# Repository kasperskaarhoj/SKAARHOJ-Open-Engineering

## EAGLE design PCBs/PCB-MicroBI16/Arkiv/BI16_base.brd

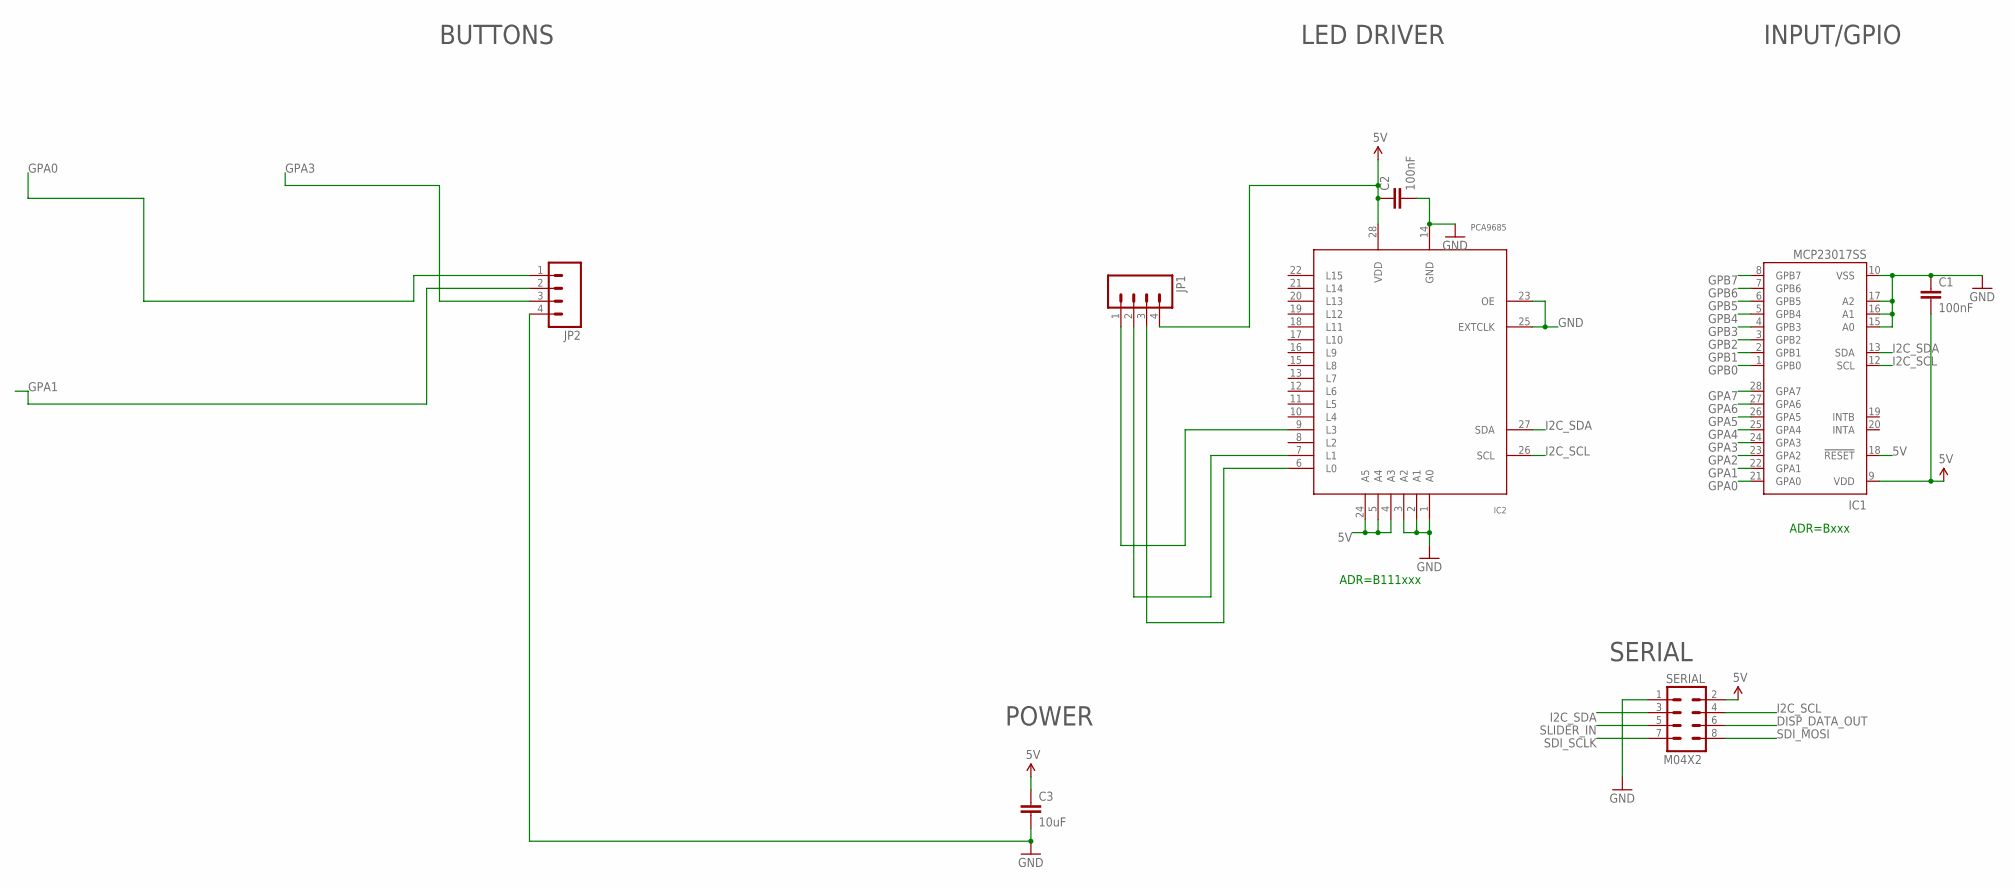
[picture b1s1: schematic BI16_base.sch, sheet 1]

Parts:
C1, C2: 100nF; 0603-CAP
C3: 10uF; 0805
IC1: MCP23017SS; SSOP28; MPN MCP23017-E/SS
IC2: PCA9685; TSSOP28
JP1, JP2: M04LOCK; 1X04_LOCK
SERIAL: M04X2; 2X4

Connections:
5V: C1.2, C2.1, C3.1, IC1.9 (VDD), IC1.18 (!RESET), IC2.4 (A3), IC2.5 (A4), IC2.24 (A5), IC2.28 (VDD), JP1.4, SERIAL.2
DISP_DATA_OUT: SERIAL.6
GND: C1.1, C2.2, C3.2, IC1.10 (VSS), IC1.15 (A0), IC1.16 (A1), IC1.17 (A2), IC2.1 (A0), IC2.2 (A1), IC2.3 (A2), IC2.14 (GND), IC2.23 (OE), IC2.25 (EXTCLK), JP2.4, SERIAL.1
GPA0: IC1.21 (GPA0), JP2.1
GPA1: IC1.22 (GPA1), JP2.2
GPA2: IC1.23 (GPA2)
GPA3: IC1.24 (GPA3), JP2.3
GPA4: IC1.25 (GPA4)
GPA5: IC1.26 (GPA5)
GPA6: IC1.27 (GPA6)
GPA7: IC1.28 (GPA7)
GPB0: IC1.1 (GPB0)
GPB1: IC1.2 (GPB1)
GPB2: IC1.3 (GPB2)
GPB3: IC1.4 (GPB3)
GPB4: IC1.5 (GPB4)
GPB5: IC1.6 (GPB5)
GPB6: IC1.7 (GPB6)
GPB7: IC1.8 (GPB7)
I2C_SCL: IC1.12 (SCL), IC2.26 (SCL), SERIAL.4
I2C_SDA: IC1.13 (SDA), IC2.27 (SDA), SERIAL.3
unnamed: IC2.9 (L3), JP1.1
unnamed: IC2.7 (L1), JP1.2
unnamed: IC2.6 (L0), JP1.3
SDI_MOSI: SERIAL.8
SDI_SCLK: SERIAL.7
SLIDER_IN: SERIAL.5

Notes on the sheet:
ADR=B111xxx
ADR=Bxxx
BUTTONS
LED DRIVER
INPUT/GPIO
POWER
SERIAL

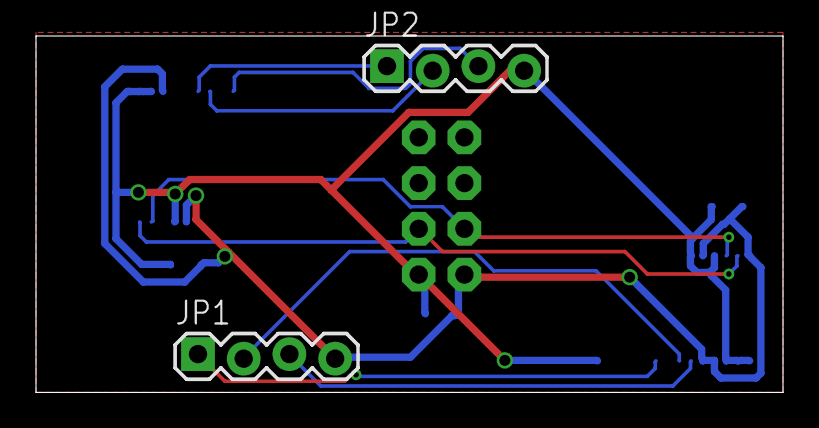
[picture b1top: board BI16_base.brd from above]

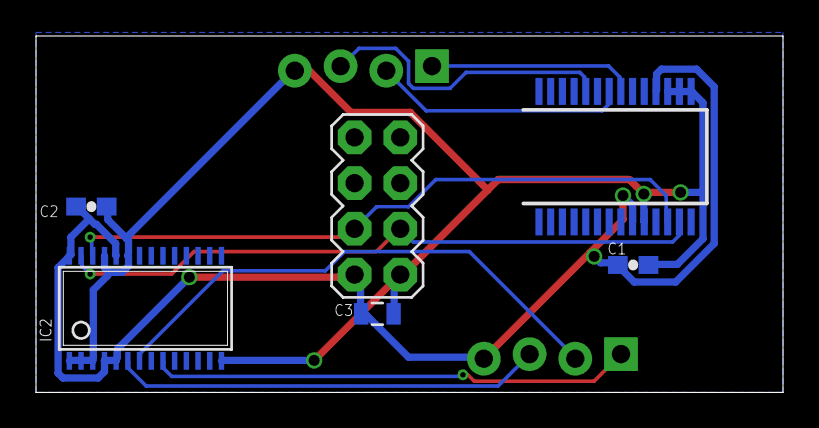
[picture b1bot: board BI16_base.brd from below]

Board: 2 copper layers, 41.5 x 19.8 mm, 8 parts (6 on the bottom side), 10 nets.

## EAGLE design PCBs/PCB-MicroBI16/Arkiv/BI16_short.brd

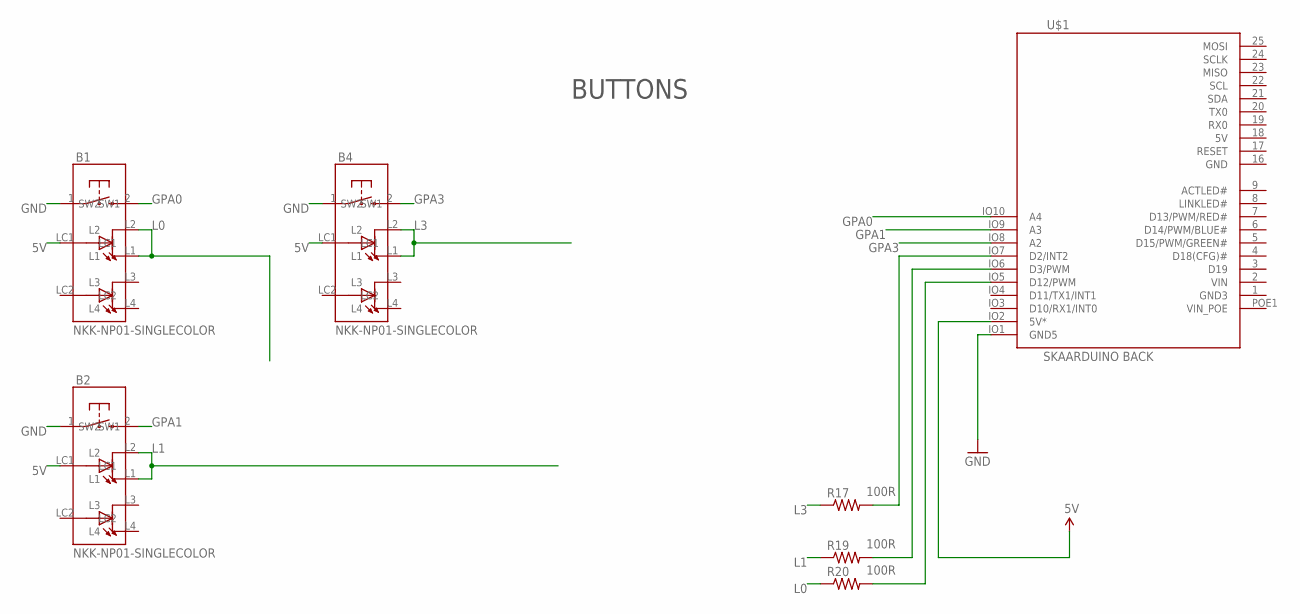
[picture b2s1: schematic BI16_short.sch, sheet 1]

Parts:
B1, B2, B4: NKK-NP01-SINGLECOLOR; NKK-NP01
R17, R19, R20: 100R; 0603-RES
U$1: SKAARDUINO_BACK_EDGECON; SKAARDUINO_BACK_PTH_EDGECON

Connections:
5V: B1.LC1, B2.LC1, B4.LC1, U$1.18 (5V), U$1.IO2 (5V*)
GND: B1.1 (SW1), B2.1 (SW1), B4.1 (SW1), U$1.16 (GND), U$1.IO1 (GND5)
GND3: U$1.1 (GND3)
GPA0: B1.2 (SW2), U$1.IO10 (A4)
GPA1: B2.2 (SW2), U$1.IO9 (A3)
GPA3: B4.2 (SW2), U$1.IO8 (A2)
L0: B1.L1, B1.L2, R20.1
L1: B2.L1, B2.L2, R19.1
L3: B4.L1, B4.L2, R17.1
unnamed: R17.2, U$1.IO7 (D2/INT2)
unnamed: R19.2, U$1.IO6 (D3/PWM)
unnamed: R20.2, U$1.IO5 (D12/PWM)
VIN: U$1.2 (VIN)
VIN_POE: U$1.POE1 (VIN_POE)

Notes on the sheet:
BUTTONS

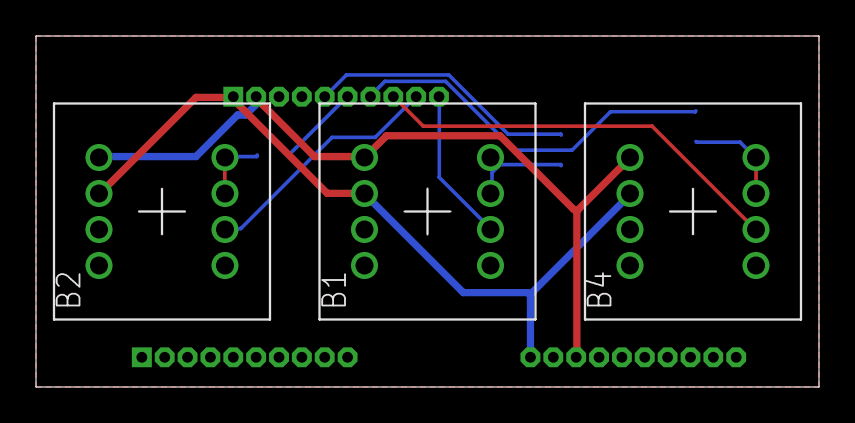
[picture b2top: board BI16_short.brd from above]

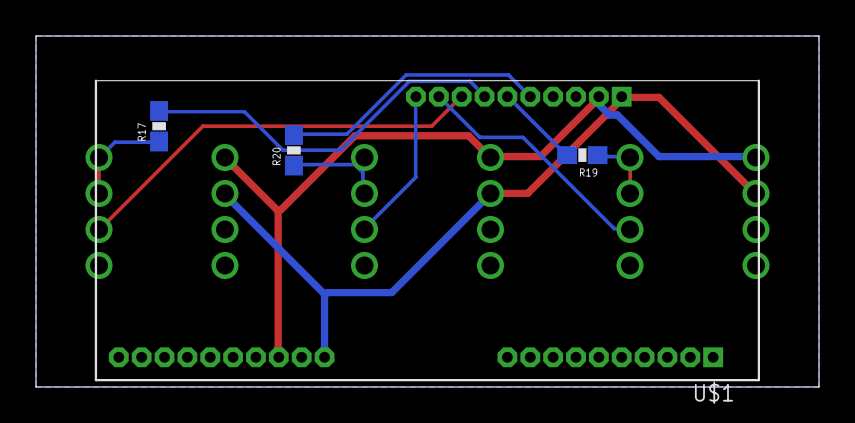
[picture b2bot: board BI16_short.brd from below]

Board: 2 copper layers, 43.5 x 19.5 mm, 7 parts (4 on the bottom side), 11 nets.

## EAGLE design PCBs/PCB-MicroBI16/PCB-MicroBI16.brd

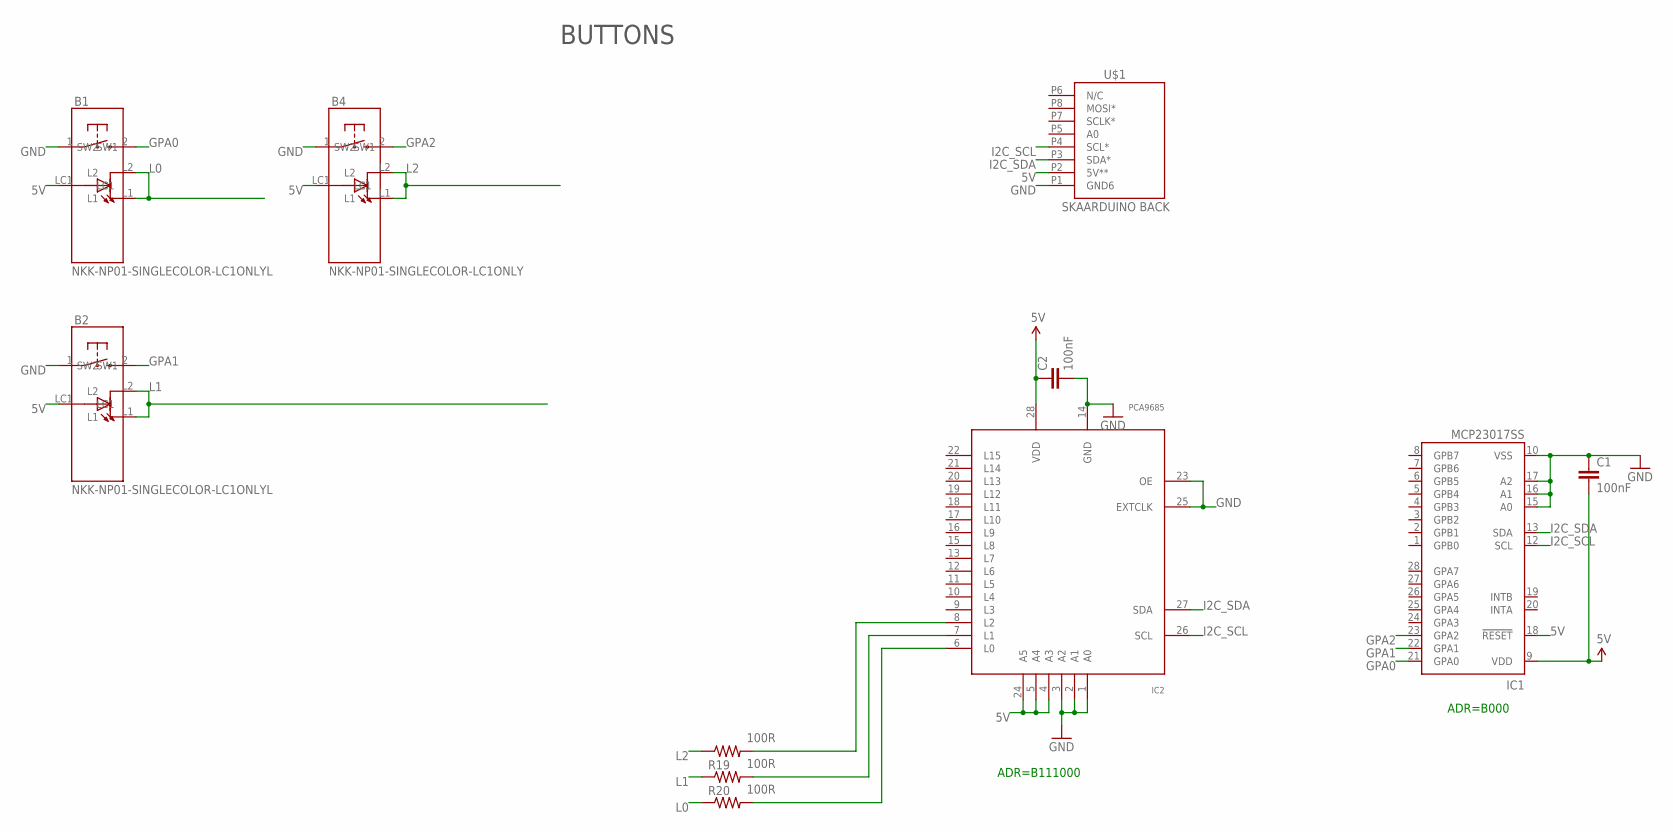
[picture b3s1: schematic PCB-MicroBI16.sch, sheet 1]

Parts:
B1, B2: NKK-NP01-SINGLECOLOR-LC1ONLYL; NKK-NP01_LESSHOLES3
B4: NKK-NP01-SINGLECOLOR-LC1ONLY; NKK-NP01_LESSHOLES2
C1, C2: 100nF; 0603-CAP
IC1: MCP23017SS; SSOP28; MPN MCP23017-E/SS
IC2: PCA9685; TSSOP28
R18, R19, R20: 100R; 0603-RES
U$1: SKAARDUINO_BACK_SERIAL; SKAARDUINO_BACK_PTH_SERIAL

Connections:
5V: B1.LC1, B2.LC1, B4.LC1, C1.2, C2.1, IC1.9 (VDD), IC1.18 (!RESET), IC2.4 (A3), IC2.5 (A4), IC2.24 (A5), IC2.28 (VDD), U$1.P2 (5V**)
GND: B1.1 (SW1), B2.1 (SW1), B4.1 (SW1), C1.1, C2.2, IC1.10 (VSS), IC1.15 (A0), IC1.16 (A1), IC1.17 (A2), IC2.1 (A0), IC2.2 (A1), IC2.3 (A2), IC2.14 (GND), IC2.23 (OE), IC2.25 (EXTCLK), U$1.P1 (GND6)
GPA0: B1.2 (SW2), IC1.21 (GPA0)
GPA1: B2.2 (SW2), IC1.22 (GPA1)
GPA2: B4.2 (SW2), IC1.23 (GPA2)
I2C_SCL: IC1.12 (SCL), IC2.26 (SCL), U$1.P4 (SCL*)
I2C_SDA: IC1.13 (SDA), IC2.27 (SDA), U$1.P3 (SDA*)
L0: B1.L1, B1.L2, R20.1
L1: B2.L1, B2.L2, R19.1
L2: B4.L1, B4.L2, R18.1
unnamed: IC2.8 (L2), R18.2
unnamed: IC2.7 (L1), R19.2
unnamed: IC2.6 (L0), R20.2

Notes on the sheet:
BUTTONS
ADR=B111000
ADR=B000

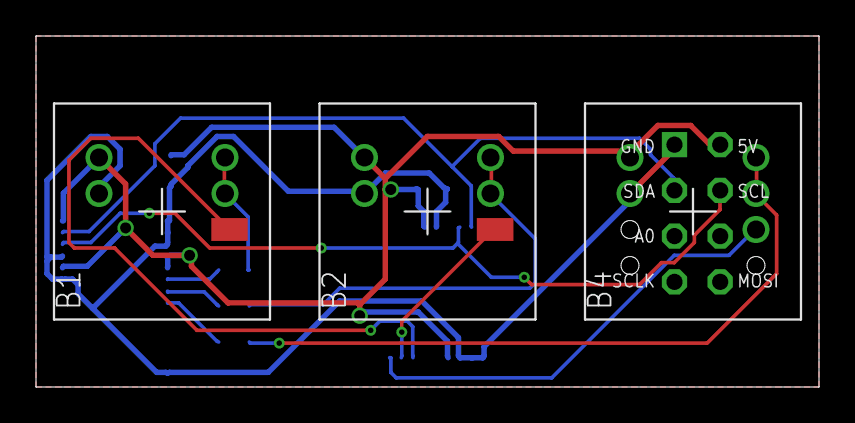
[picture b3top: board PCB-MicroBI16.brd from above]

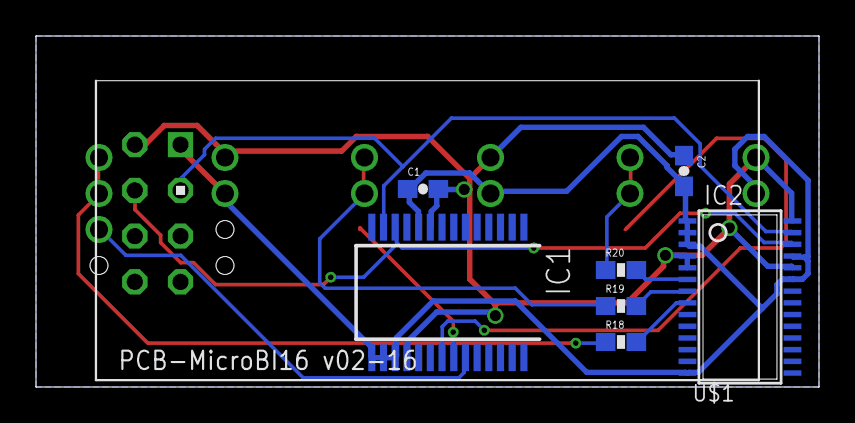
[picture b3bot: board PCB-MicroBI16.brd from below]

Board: 2 copper layers, 43.5 x 19.5 mm, 11 parts (8 on the bottom side), 13 nets.

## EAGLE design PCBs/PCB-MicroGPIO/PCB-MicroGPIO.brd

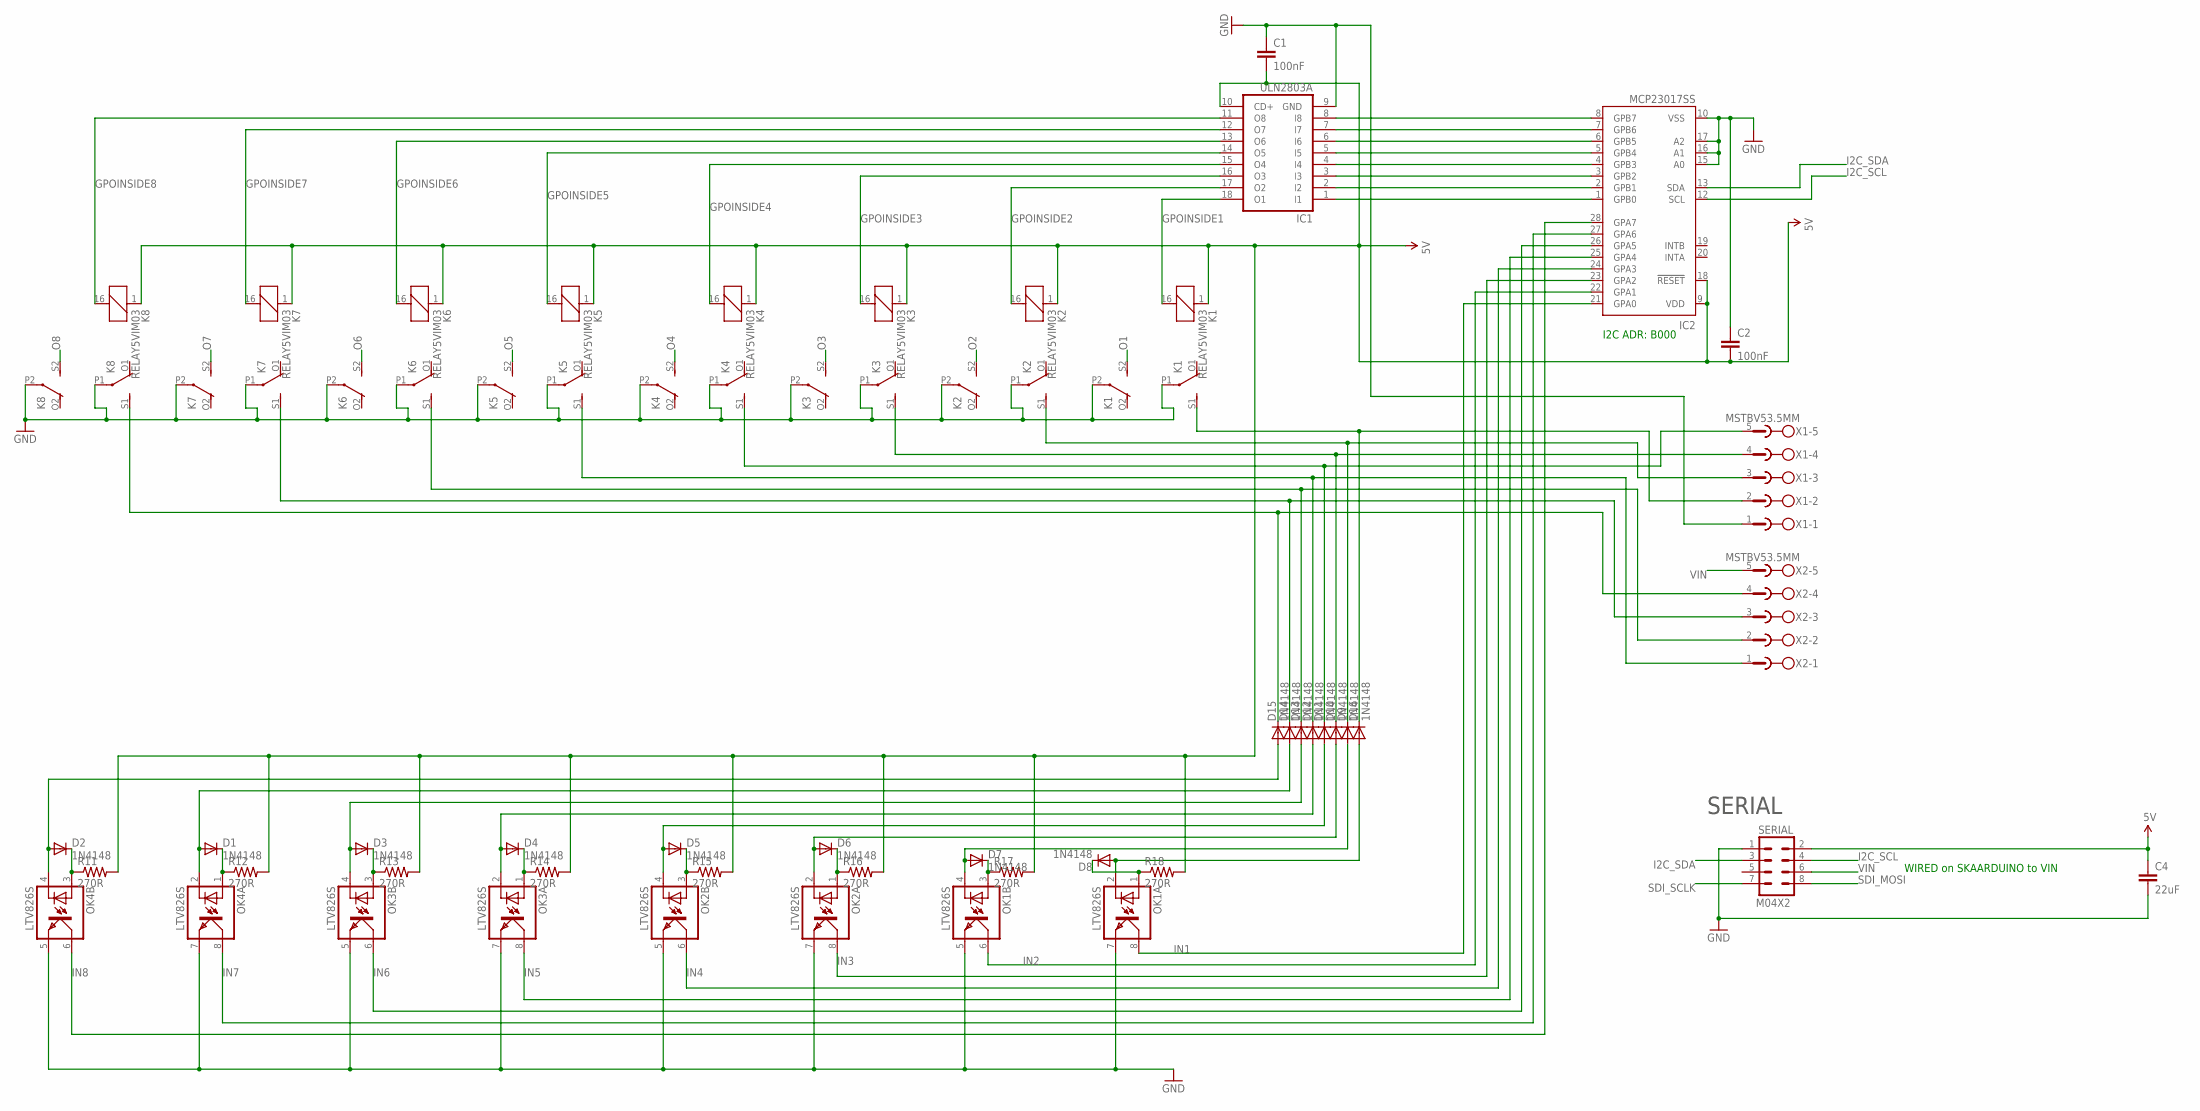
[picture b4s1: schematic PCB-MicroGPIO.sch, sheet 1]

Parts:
C1, C2: 100nF; 0603-CAP
C4: 22uF; 0805
D1, D2, D3, D4, D5, D6, D7, D8, D9, D10, D11, D12, D13, D14, D15, D16: 1N4148; SOD-323
IC1: ULN2803A; SO18W
IC2: MCP23017SS; SSOP28
K1, K2, K3, K4, K5, K6, K7, K8: RELAY5VIM03; DS2Y
OK1, OK2, OK3, OK4: LTV826S; DIL8-SMD
R11, R12, R13, R14, R15, R16, R17, R18: 270R; 0603-RES
SERIAL: M04X2; 2X4
X1, X2: MSTBV53.5MM; MSTBV5-3.5

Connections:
5V: C1.2, C2.2, C4.1, IC1.10 (CD+), IC2.9 (VDD), IC2.18 (!RESET), K1.1, K2.1, K3.1, K4.1, K5.1, K6.1, K7.1, K8.1, R11.2, R12.2, R13.2, R14.2, R15.2, R16.2, R17.2, R18.2, SERIAL.2
GND: C1.1, C2.1, C4.2, IC1.9 (GND), IC2.10 (VSS), IC2.15 (A0), IC2.16 (A1), IC2.17 (A2), K1.P1, K1.P2, K2.P1, K2.P2, K3.P1, K3.P2, K4.P1, K4.P2, K5.P1, K5.P2, K6.P1, K6.P2, K7.P1, K7.P2, K8.P1, K8.P2, OK1.5 (EMIT), OK1.7 (EMIT), OK2.5 (EMIT), OK2.7 (EMIT), OK3.5 (EMIT), OK3.7 (EMIT), OK4.5 (EMIT), OK4.7 (EMIT), SERIAL.1, X1.1
GPOINSIDE1: IC1.18 (O1), K1.16 (2)
GPOINSIDE2: IC1.17 (O2), K2.16 (2)
GPOINSIDE3: IC1.16 (O3), K3.16 (2)
GPOINSIDE4: IC1.15 (O4), K4.16 (2)
GPOINSIDE5: IC1.14 (O5), K5.16 (2)
GPOINSIDE6: IC1.13 (O6), K6.16 (2)
GPOINSIDE7: IC1.12 (O7), K7.16 (2)
GPOINSIDE8: IC1.11 (O8), K8.16 (2)
I2C_SCL: IC2.12 (SCL), SERIAL.4
I2C_SDA: IC2.13 (SDA), SERIAL.3
IN1: IC2.21 (GPA0), OK1.8 (COL)
IN2: IC2.22 (GPA1), OK1.6 (COL)
IN3: IC2.23 (GPA2), OK2.8 (COL)
IN4: IC2.24 (GPA3), OK2.6 (COL)
IN5: IC2.25 (GPA4), OK3.8 (COL)
IN6: IC2.26 (GPA5), OK3.6 (COL)
IN7: IC2.27 (GPA6), OK4.8 (COL)
IN8: IC2.28 (GPA7), OK4.6 (COL)
unnamed: D2.2 (A), D15.2 (A), OK4.4 (C)
unnamed: D1.2 (A), D14.2 (A), OK4.2 (C)
unnamed: D3.2 (A), D13.2 (A), OK3.4 (C)
unnamed: D4.2 (A), D12.2 (A), OK3.2 (C)
unnamed: IC1.1 (I1), IC2.1 (GPB0)
unnamed: D5.2 (A), D11.2 (A), OK2.4 (C)
unnamed: D6.2 (A), D10.2 (A), OK2.2 (C)
unnamed: D7.2 (A), D9.2 (A), OK1.4 (C)
unnamed: D8.2 (A), D16.2 (A), OK1.2 (C)
unnamed: D2.1 (C), OK4.3 (A), R11.1
unnamed: D1.1 (C), OK4.1 (A), R12.1
unnamed: D3.1 (C), OK3.3 (A), R13.1
unnamed: D4.1 (C), OK3.1 (A), R14.1
unnamed: D5.1 (C), OK2.3 (A), R15.1
unnamed: D6.1 (C), OK2.1 (A), R16.1
unnamed: D7.1 (C), OK1.3 (A), R17.1
unnamed: D8.1 (C), OK1.1 (A), R18.1
unnamed: IC1.2 (I2), IC2.2 (GPB1)
unnamed: IC1.3 (I3), IC2.3 (GPB2)
unnamed: IC1.4 (I4), IC2.4 (GPB3)
unnamed: IC1.5 (I5), IC2.5 (GPB4)
unnamed: IC1.6 (I6), IC2.6 (GPB5)
unnamed: IC1.7 (I7), IC2.7 (GPB6)
unnamed: IC1.8 (I8), IC2.8 (GPB7)
unnamed: D16.1 (C), K1.S1 (S), X1.2
unnamed: D12.1 (C), K5.S1 (S), X2.1
unnamed: D9.1 (C), K2.S1 (S), X1.3
unnamed: D10.1 (C), K3.S1 (S), X1.4
unnamed: D11.1 (C), K4.S1 (S), X1.5
unnamed: D13.1 (C), K6.S1 (S), X2.2
unnamed: D14.1 (C), K7.S1 (S), X2.3
unnamed: D15.1 (C), K8.S1 (S), X2.4
O1: K1.S2 (S)
O2: K2.S2 (S)
O3: K3.S2 (S)
O4: K4.S2 (S)
O5: K5.S2 (S)
O6: K6.S2 (S)
O7: K7.S2 (S)
O8: K8.S2 (S)
SDI_MOSI: SERIAL.8
SDI_SCLK: SERIAL.7
VIN: SERIAL.6, X2.5

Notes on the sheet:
I2C ADR: B000
SERIAL
WIRED on SKAARDUINO to VIN

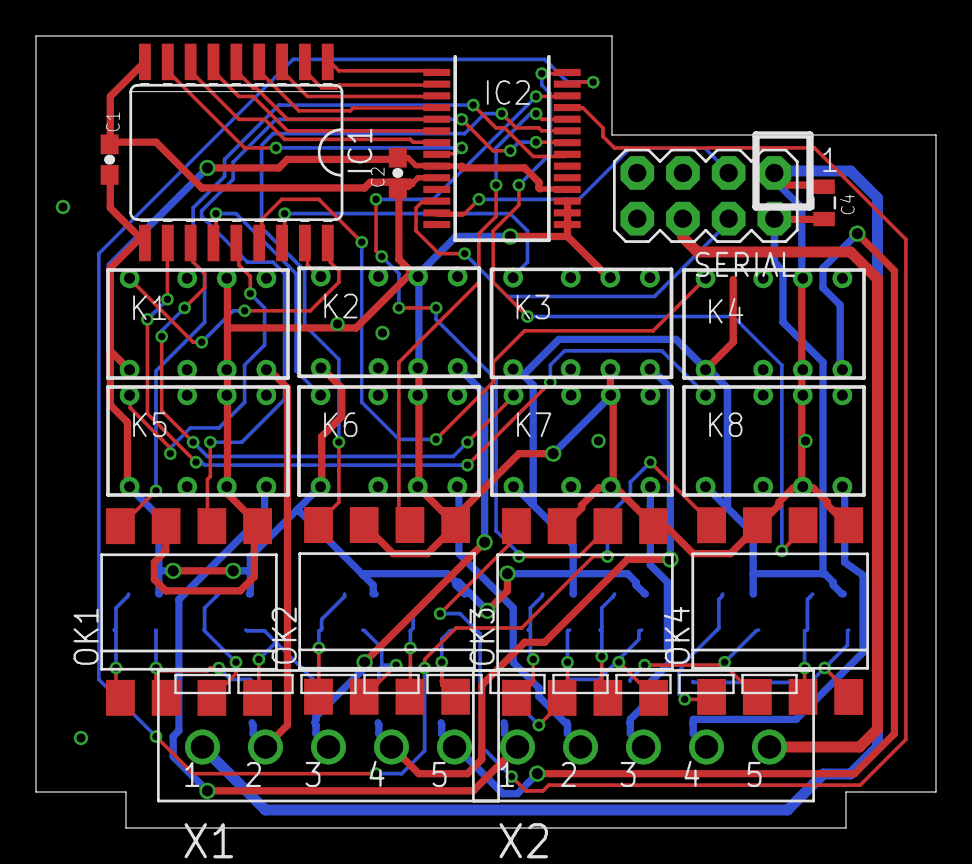
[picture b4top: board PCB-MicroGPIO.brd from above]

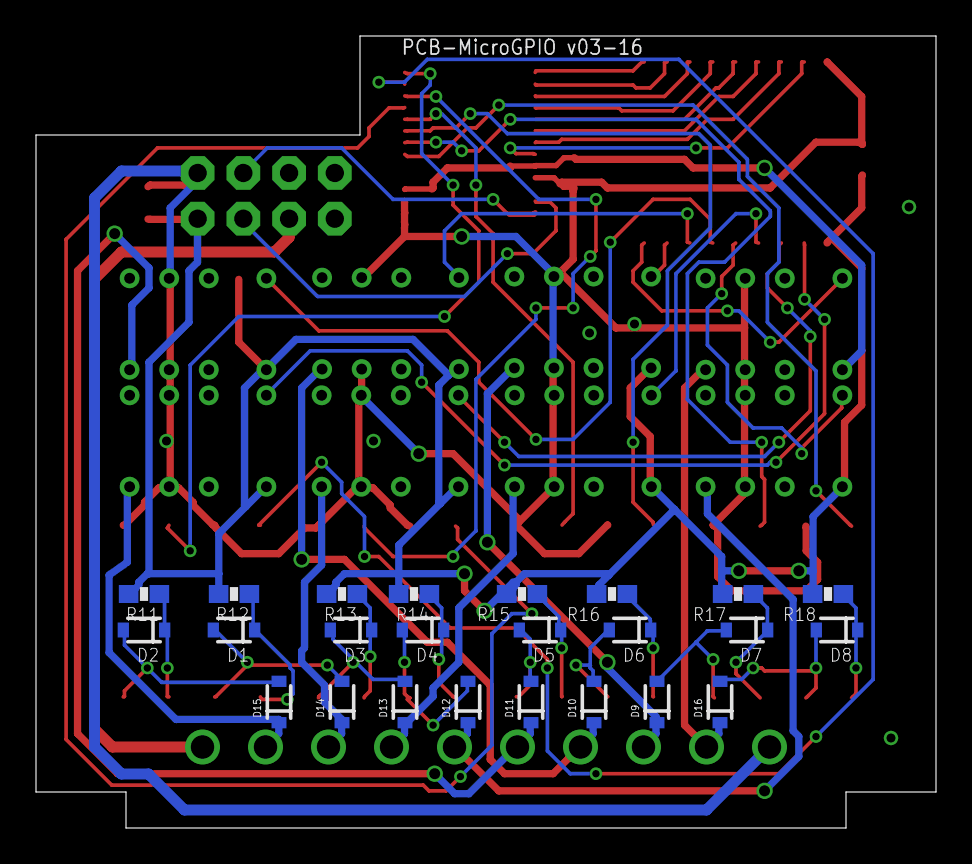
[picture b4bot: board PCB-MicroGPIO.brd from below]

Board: 2 copper layers, 50.0 x 44.0 mm, 44 parts (24 on the bottom side), 53 nets.

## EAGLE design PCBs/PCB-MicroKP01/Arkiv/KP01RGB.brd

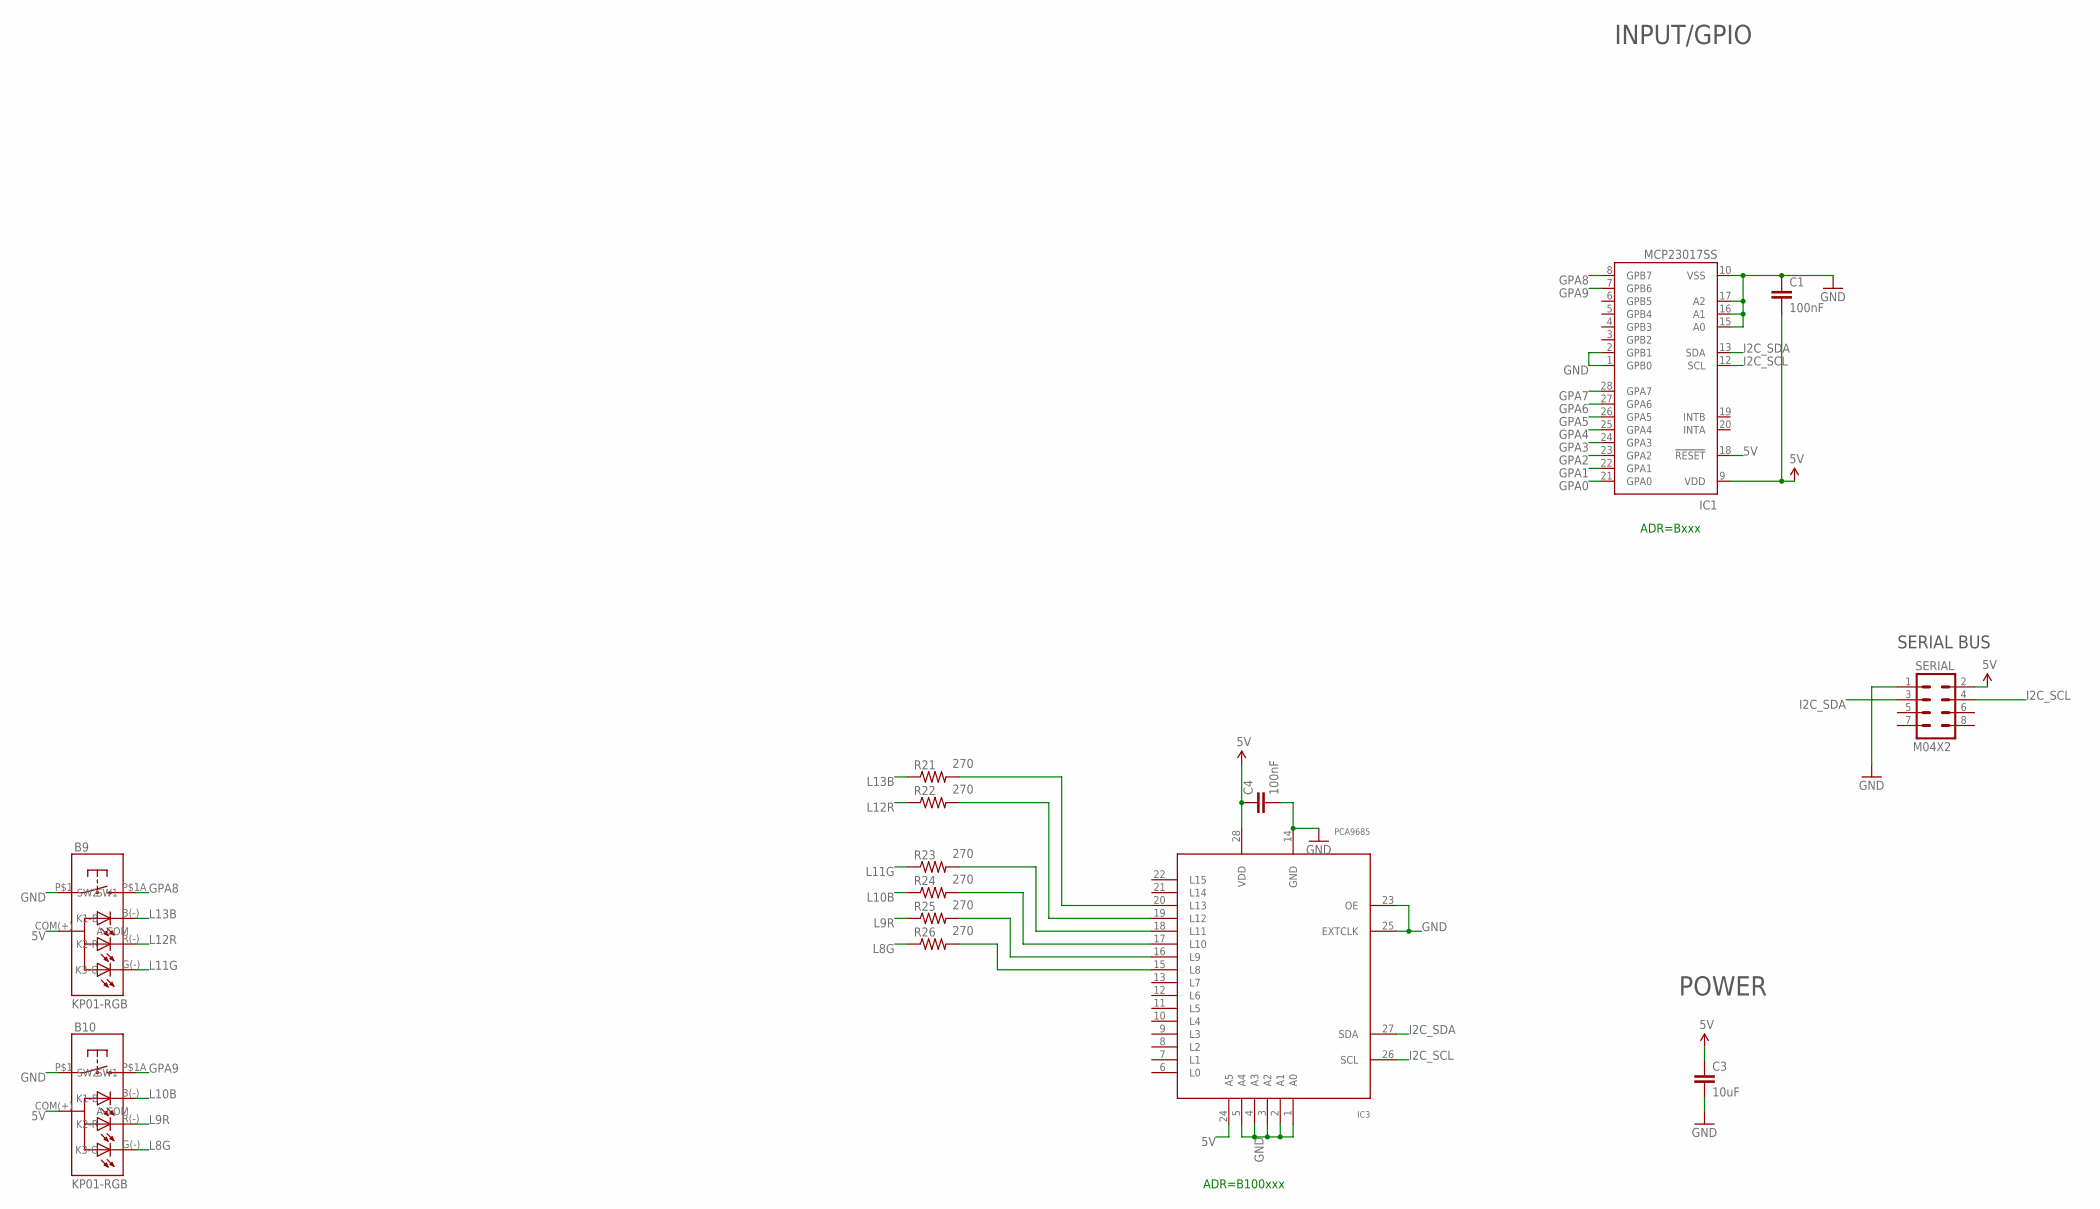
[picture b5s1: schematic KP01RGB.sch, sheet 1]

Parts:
B9, B10: KP01-RGB; NKK-KP01
C1, C4: 100nF; 0603-CAP
C3: 10uF; 0805
IC1: MCP23017SS; SSOP28; MPN MCP23017-E/SS
IC3: PCA9685; TSSOP28
R21, R22, R23, R24, R25, R26: 270; 0603-RES
SERIAL: M04X2; 2X4

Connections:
5V: B9.COM(+) (A-COM), B10.COM(+) (A-COM), C1.2, C3.1, C4.1, IC1.9 (VDD), IC1.18 (!RESET), IC3.24 (A5), IC3.28 (VDD), SERIAL.2
GND: B9.P$1 (SW1), B10.P$1 (SW1), C1.1, C3.2, C4.2, IC1.1 (GPB0), IC1.2 (GPB1), IC1.10 (VSS), IC1.15 (A0), IC1.16 (A1), IC1.17 (A2), IC3.1 (A0), IC3.2 (A1), IC3.3 (A2), IC3.4 (A3), IC3.5 (A4), IC3.14 (GND), IC3.23 (OE), IC3.25 (EXTCLK), SERIAL.1
GPA0: IC1.21 (GPA0)
GPA1: IC1.22 (GPA1)
GPA2: IC1.23 (GPA2)
GPA3: IC1.24 (GPA3)
GPA4: IC1.25 (GPA4)
GPA5: IC1.26 (GPA5)
GPA6: IC1.27 (GPA6)
GPA7: IC1.28 (GPA7)
GPA8: B9.P$1A (SW2), IC1.8 (GPB7)
GPA9: B10.P$1A (SW2), IC1.7 (GPB6)
I2C_SCL: IC1.12 (SCL), IC3.26 (SCL), SERIAL.4
I2C_SDA: IC1.13 (SDA), IC3.27 (SDA), SERIAL.3
L8G: B10.G(-) (K3-G), R26.1
L9R: B10.R(-) (K2-R), R25.1
L10B: B10.B(-) (K1-B), R24.1
L11G: B9.G(-) (K3-G), R23.1
L12R: B9.R(-) (K2-R), R22.1
L13B: B9.B(-) (K1-B), R21.1
unnamed: IC3.15 (L8), R26.2
unnamed: IC3.16 (L9), R25.2
unnamed: IC3.17 (L10), R24.2
unnamed: IC3.18 (L11), R23.2
unnamed: IC3.19 (L12), R22.2
unnamed: IC3.20 (L13), R21.2

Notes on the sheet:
SERIAL BUS
ADR=Bxxx
INPUT/GPIO
POWER
ADR=B100xxx

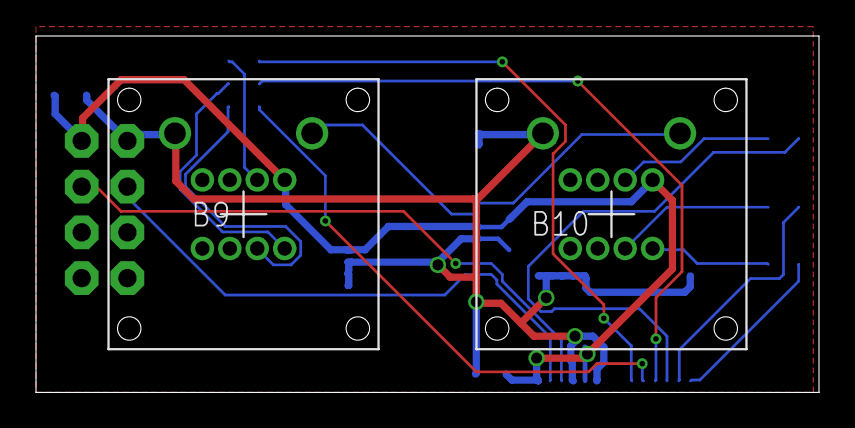
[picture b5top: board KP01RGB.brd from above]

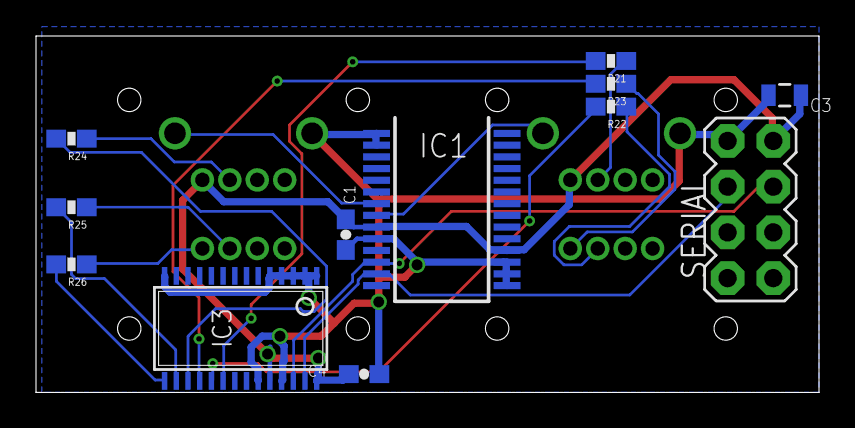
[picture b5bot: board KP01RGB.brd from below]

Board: 2 copper layers, 43.5 x 19.8 mm, 14 parts (12 on the bottom side), 18 nets.

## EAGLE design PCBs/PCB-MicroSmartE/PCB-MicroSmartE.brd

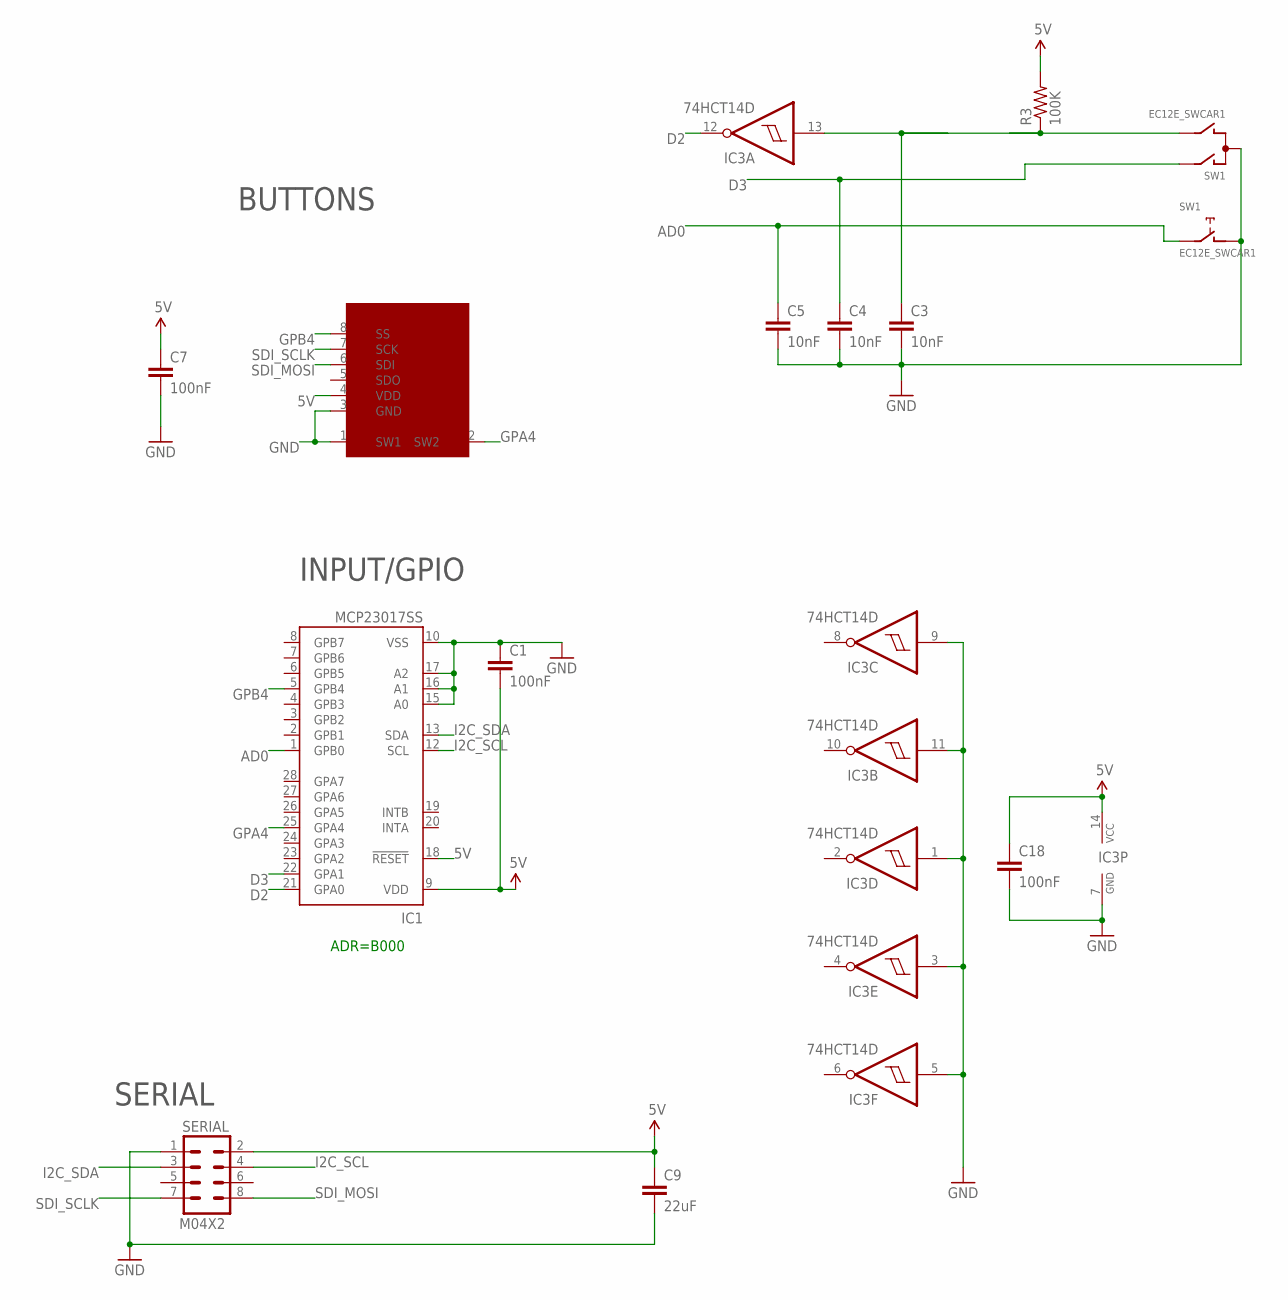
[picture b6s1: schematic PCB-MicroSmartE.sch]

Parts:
C1, C7, C18: 100nF; 0603-CAP
C3, C4, C5: 10nF; 0603-CAP
C9: 22uF; 0805
IC1: MCP23017SS; SSOP28; MPN MCP23017-E/SS
IC3: 74HCT14D; SO14
R3: 100K; 0603-RES
SERIAL: M04X2; 2X4
SSW1: SMART_SWITCHSMART_SWITCH_8PIN; SMART_SWITCH
SW1: EC12E_SWCAR1; ALPS_EC12E_SW-CAR1

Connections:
5V: C1.2, C7.1, C9.1, C18.1, IC1.9 (VDD), IC1.18 (!RESET), IC3.14 (VCC), R3.2, SERIAL.2, SSW1.4 (VDD)
AD0: C5.1, IC1.1 (GPB0), SW1.E (2)
D2: IC1.21 (GPA0), IC3.12 (O)
D3: C4.1, IC1.22 (GPA1), SW1.A
GND: C1.1, C3.2, C4.2, C5.2, C7.2, C9.2, C18.2, IC1.10 (VSS), IC1.15 (A0), IC1.16 (A1), IC1.17 (A2), IC3.1 (I), IC3.3 (I), IC3.5 (I), IC3.7 (GND), IC3.9 (I), IC3.11 (I), SERIAL.1, SSW1.1 (SW1), SSW1.3 (GND), SW1.C, SW1.D (1)
GPA4: IC1.25 (GPA4), SSW1.2 (SW2)
GPB4: IC1.5 (GPB4), SSW1.8 (SS)
I2C_SCL: IC1.12 (SCL), SERIAL.4
I2C_SDA: IC1.13 (SDA), SERIAL.3
unnamed: C3.1, IC3.13 (I), R3.1, SW1.B
SDI_MOSI: SERIAL.8, SSW1.6 (SDI)
SDI_SCLK: SERIAL.7, SSW1.7 (SCK)

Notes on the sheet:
ADR=B000
INPUT/GPIO
SERIAL
BUTTONS

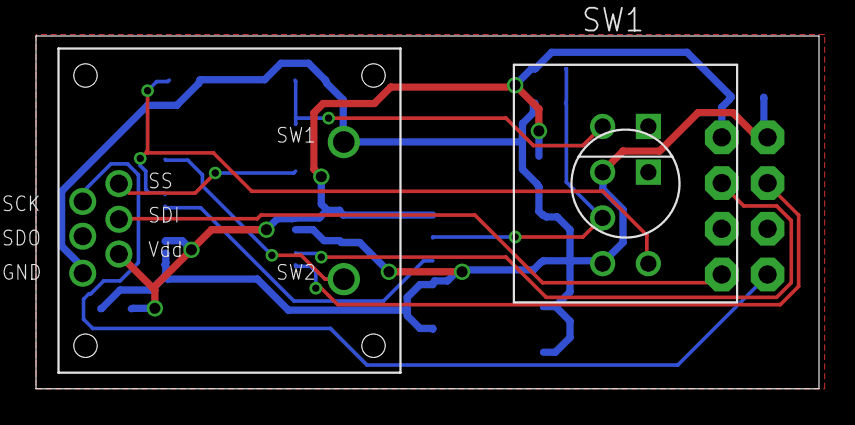
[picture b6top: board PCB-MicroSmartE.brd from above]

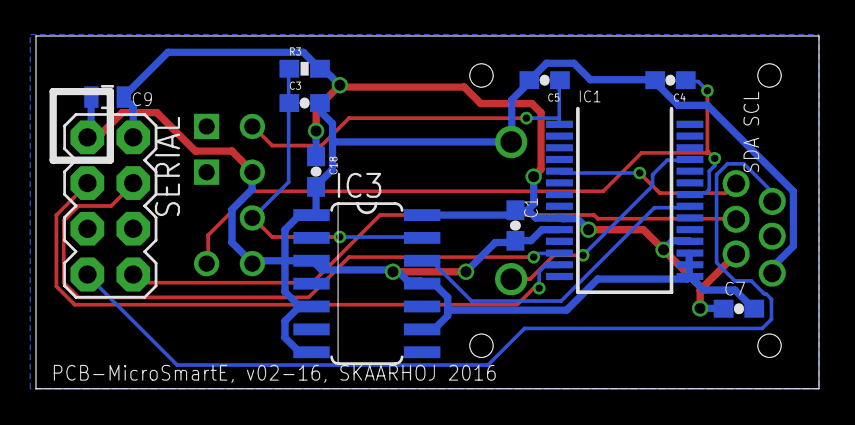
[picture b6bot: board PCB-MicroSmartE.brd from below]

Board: 2 copper layers, 43.5 x 19.6 mm, 13 parts (11 on the bottom side), 12 nets.

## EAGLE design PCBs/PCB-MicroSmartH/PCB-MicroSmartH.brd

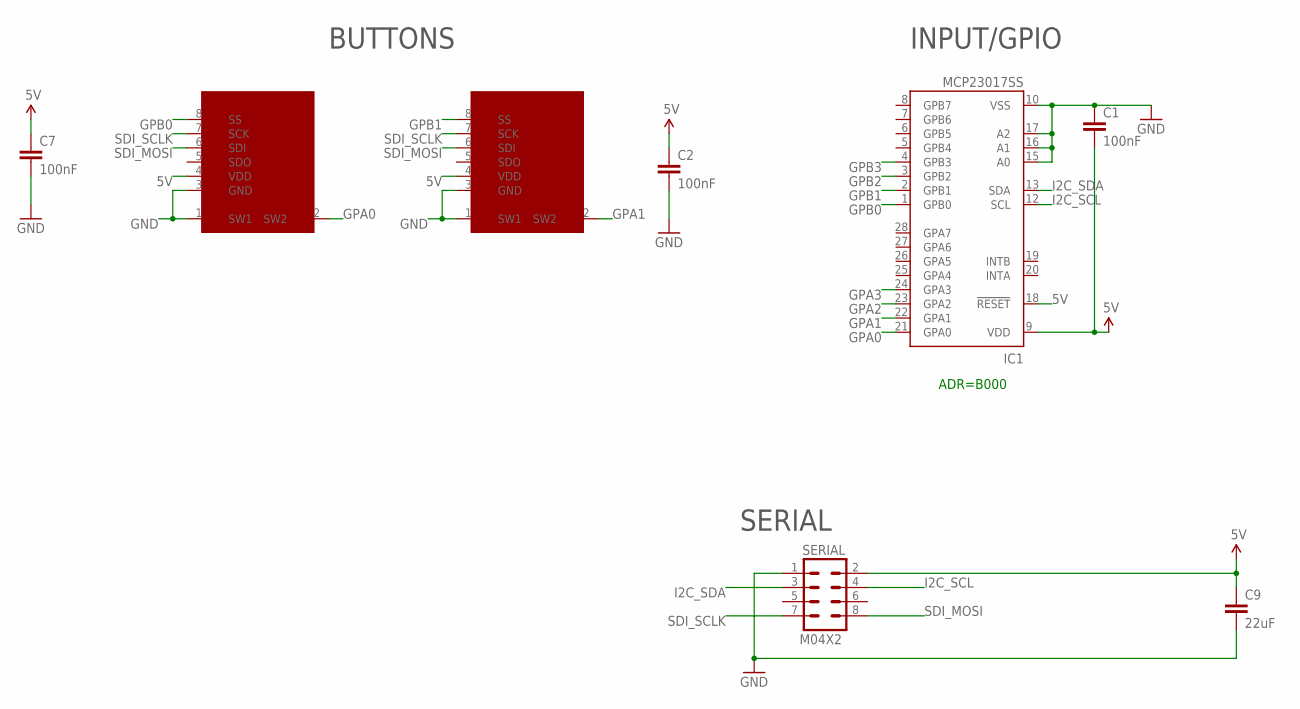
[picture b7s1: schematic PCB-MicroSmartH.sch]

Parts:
C1, C2, C7: 100nF; 0603-CAP
C9: 22uF; 0805
IC1: MCP23017SS; SSOP28; MPN MCP23017-E/SS
SERIAL: M04X2; 2X4
SSW1, SSW2: SMART_SWITCHSMART_SWITCH_8PIN; SMART_SWITCH

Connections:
5V: C1.2, C2.1, C7.1, C9.1, IC1.9 (VDD), IC1.18 (!RESET), SERIAL.2, SSW1.4 (VDD), SSW2.4 (VDD)
GND: C1.1, C2.2, C7.2, C9.2, IC1.10 (VSS), IC1.15 (A0), IC1.16 (A1), IC1.17 (A2), SERIAL.1, SSW1.1 (SW1), SSW1.3 (GND), SSW2.1 (SW1), SSW2.3 (GND)
GPA0: IC1.21 (GPA0), SSW1.2 (SW2)
GPA1: IC1.22 (GPA1), SSW2.2 (SW2)
GPA2: IC1.23 (GPA2)
GPA3: IC1.24 (GPA3)
GPB0: IC1.1 (GPB0), SSW1.8 (SS)
GPB1: IC1.2 (GPB1), SSW2.8 (SS)
GPB2: IC1.3 (GPB2)
GPB3: IC1.4 (GPB3)
I2C_SCL: IC1.12 (SCL), SERIAL.4
I2C_SDA: IC1.13 (SDA), SERIAL.3
SDI_MOSI: SERIAL.8, SSW1.6 (SDI), SSW2.6 (SDI)
SDI_SCLK: SERIAL.7, SSW1.7 (SCK), SSW2.7 (SCK)

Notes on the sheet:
ADR=B000
INPUT/GPIO
SERIAL
BUTTONS

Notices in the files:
parts and their libraries:
SparkFun: Licensing: CC v3.0 Share-Alike You are welcome to use this library for commercial purposes.
